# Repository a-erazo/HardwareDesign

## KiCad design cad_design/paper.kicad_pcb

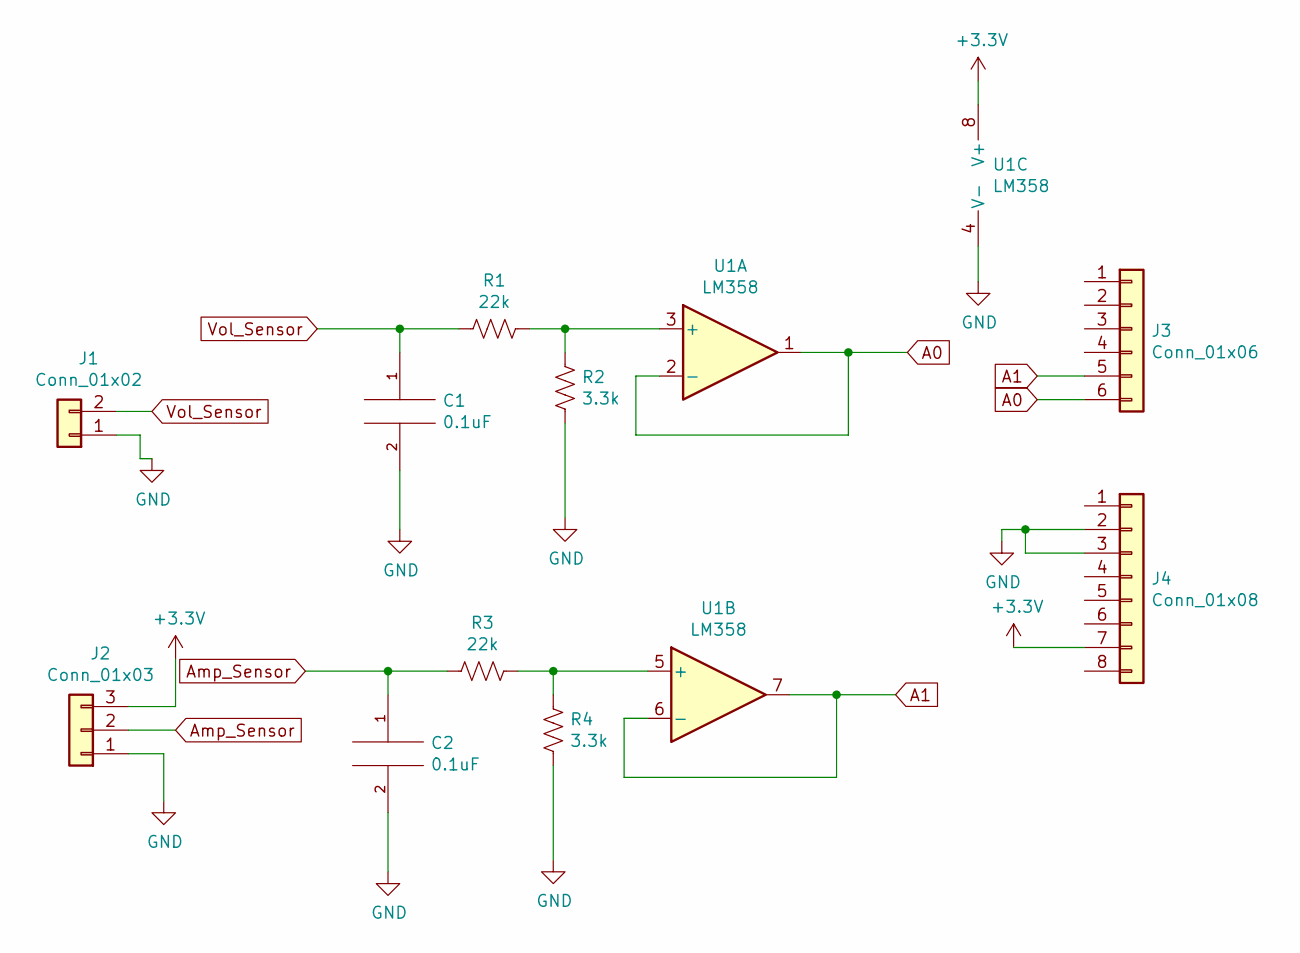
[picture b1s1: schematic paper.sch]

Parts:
C1, C2: 0.1uF; C_1206_3216Metric_Pad1.42x1.75mm_HandSolder
J1: Conn_01x02; SolderWirePad_1x02_P5.08mm_Drill1.5mm
J2: Conn_01x03; SolderWirePad_1x04_P5.08mm_Drill1.5mm
J3: Conn_01x06; PinSocket_1x06_P2.54mm_Vertical
J4: Conn_01x08; PinSocket_1x08_P2.54mm_Vertical
R1, R3: 22k; R_1206_3216Metric
R2, R4: 3.3k; R_1206_3216Metric
U1: LM358; DIP-8_W7.62mm_SMDSocket_SmallPads

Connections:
+3V3: J2.3, J4.7, U1.8 (V+)
A0: J3.6, U1.1, U1.2 (-)
A1: J3.5, U1.6 (-), U1.7
Amp_Sensor: C2.1, J2.2, R3.2
GND: C1.2, C2.2, J1.1, J2.1, J4.2, J4.3, R2.2, R4.2, U1.4 (V-)
unnamed: R1.1, R2.1, U1.3 (+)
unnamed: R3.1, R4.1, U1.5 (+)
Vol_Sensor: C1.1, J1.2, R1.2

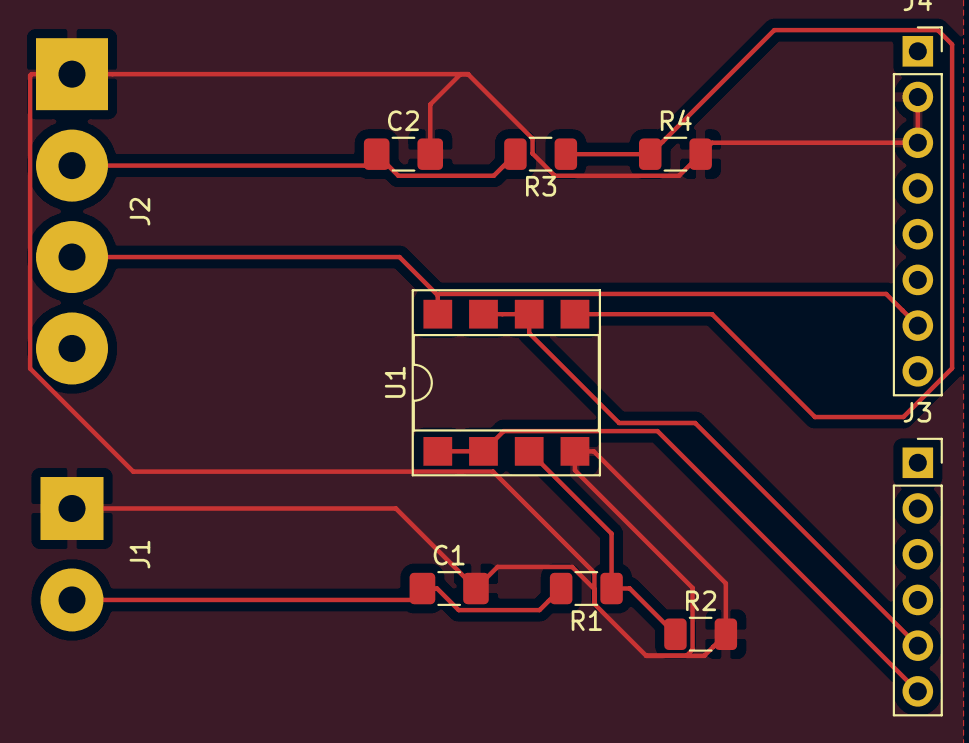
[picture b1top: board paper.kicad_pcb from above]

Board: 2 copper layers, 11 parts (0 on the bottom side), 8 nets.

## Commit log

2020-01-08 Commit de la Simulación y el diseño CAD
    En este commit se presenta todos los elementos de simulación en el
    programa Proteus y el diseño CAD en el programa kiCAD.
2020-01-09 Segundo Commit
    En este commit se presenta el diseño de la tarjeta impresa para la
    adecuación de las señales de voltaje y corriente, para empezar la
    implementación.
